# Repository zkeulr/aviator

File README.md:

# README

## Design Document

## To-do

Update design document to reflect final project
Remove DS3231 from parts list in processing subsystem
Update specifications in processing subsystem

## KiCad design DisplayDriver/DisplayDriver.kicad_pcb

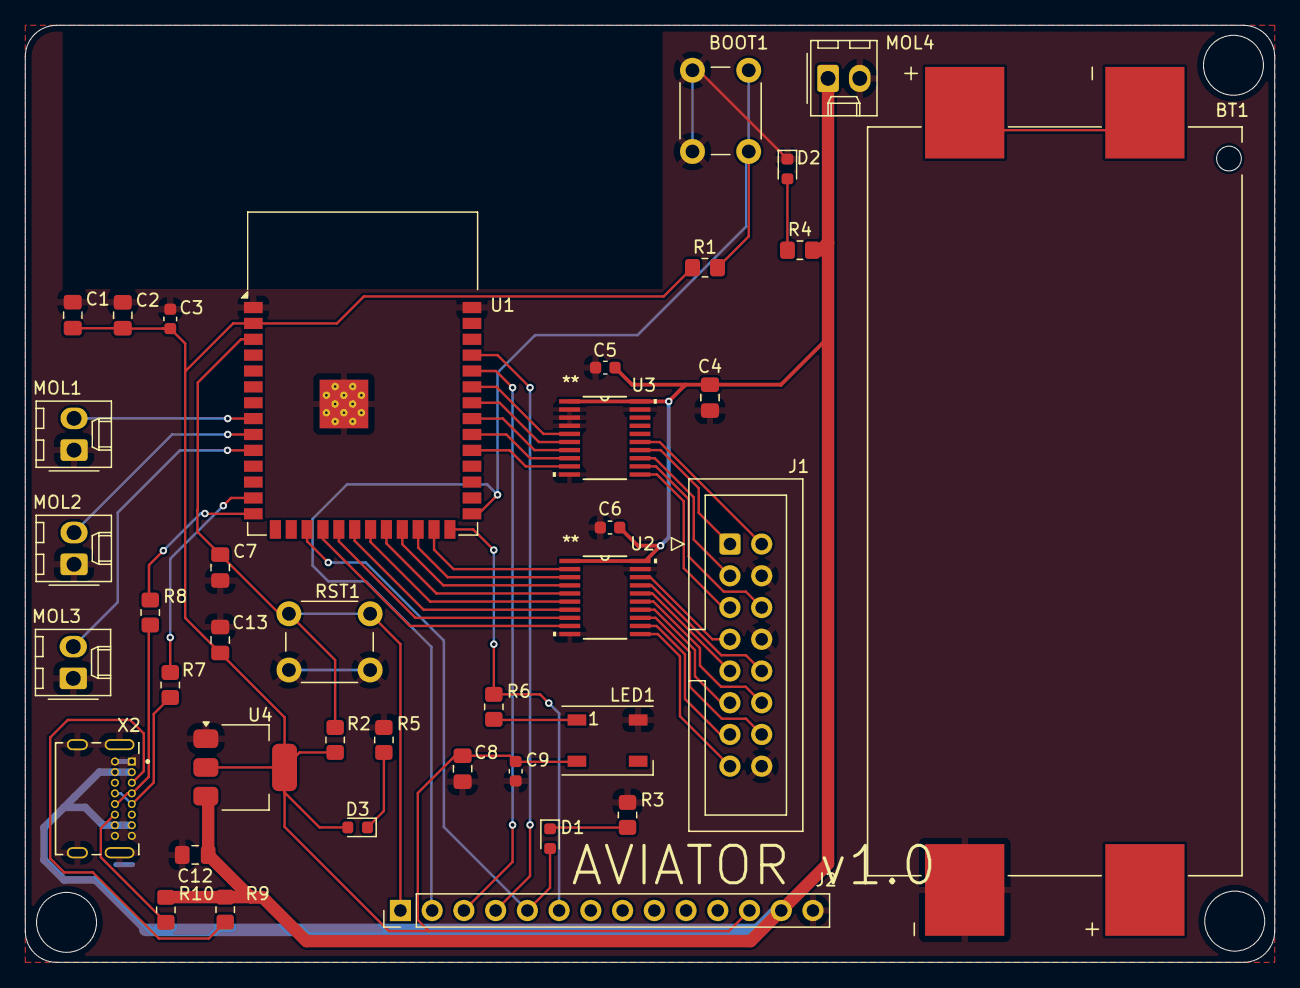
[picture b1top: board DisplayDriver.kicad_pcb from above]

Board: 2 copper layers, 100.0 x 75.0 mm, 39 parts (0 on the bottom side), 49 nets.

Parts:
BOOT1: Lab Kit; SW_PUSH_6mm
BT1: 1012; BAT_1012
C1, C4: 10uF; C_0805_2012Metric_Pad1.18x1.45mm_HandSolder
C2, C7: 1uF; C_0805_2012Metric_Pad1.18x1.45mm_HandSolder
C3, C5, C6, C9: 0.1uF; C_0603_1608Metric
C8: 100uF; C_0805_2012Metric_Pad1.18x1.45mm_HandSolder
C12, C13: C; C_0805_2012Metric_Pad1.18x1.45mm_HandSolder
D1: RED; LED_0603_1608Metric
D2, D3: GREEN; LED_0603_1608Metric
J1: HTSS-108-01-G-D; IDC-Header_2x08_P2.54mm_Vertical
J2: HEADER-1X14; PinHeader_1x14_P2.54mm_Vertical
LED1: LED_WS2812B_PLCC4_5.0x5.0mm_P3.2mm
MOL1, MOL2, MOL3: CASE_SW; Molex_KK-254_AE-6410-02A_1x02_P2.54mm_Vertical
MOL4: Vin; Molex_KK-254_AE-6410-02A_1x02_P2.54mm_Vertical
R1, R2, R3, R4, R5: 10K; R_0805_2012Metric_Pad1.20x1.40mm_HandSolder
R6: 330; R_0805_2012Metric_Pad1.20x1.40mm_HandSolder
R7, R8: 22; R_0805_2012Metric_Pad1.20x1.40mm_HandSolder
R9, R10: 56k; R_0805_2012Metric_Pad1.20x1.40mm_HandSolder
RST1: Lab Kit; SW_PUSH_6mm
U1: ESP32-S3-WROOM-1
U2, U3: 74AHCT245; PW20
U4: AMS1117-3.3; SOT-223-3_TabPin2
X2: UJ20-C-H-G-SMT-TR; CUI_UJ20-C-H-G-SMT-TR

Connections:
3.3V: C1.2, C2.2, C3.1, C8.2, C9.1, C13.1, D3.2 (A), J2.12, LED1.2 (VDD), R1.2, R2.2, U1.2 (3V3), U4.2 (VO)
+5V: C4.2, C5.1, C6.1, C12.1, J2.13, MOL4.1, R4.1, R9.1, R10.2, U2.1 (T/R), U2.20 (VCC), U3.1 (T/R), U3.20 (VCC), U4.3 (VI), X2.A4 (VBUS), X2.A9 (VBUS), X2.B4 (VBUS), X2.B9 (VBUS)
/A0: MOL1.2, U1.8 (IO15)
/A1: MOL2.2, U1.9 (IO16)
/A2: MOL3.2, U1.10 (IO17)
/ADDRA_3V: U1.23 (IO21), U2.4 (A3)
/ADDRB_3V: U1.24 (IO47), U2.3 (A2)
/ADDRC_3V: U1.21 (IO13), U2.6 (A5)
/ADDRD_3V: U1.22 (IO14), U2.5 (A4)
/B1_3V: U1.33 (IO40), U3.7 (A6)
/B2_3V: U1.25 (IO48), U2.2 (A1)
/BOOT0: BOOT1.1, J2.2, R1.1, U1.27 (IO0)
/CC1B: R9.2, X2.A5 (CC1)
/CC2B: R10.1, X2.B5 (CC2)
/CLK: J1.13, U2.12 (B7)
/CLK_3V: U1.19 (IO11), U2.8 (A7)
/D9: D1.2 (A), J2.5, U1.17 (IO9)
/DB+: R8.2, U1.14 (IO20)
/DB-: R7.2, U1.13 (IO19)
/DN_B: R7.1, X2.A7 (DN1), X2.B7 (DN2)
/DP_B: R8.1, X2.A6 (DP1), X2.B6 (DP2)
/G1_3V: U1.35 (IO42), U3.5 (A4)
/G2_3V: U1.32 (IO39), U3.8 (A7)
/LAT: J1.14, U2.13 (B6)
/LAT_3V: U1.20 (IO12), U2.7 (A6)
/M1_A: J1.09, U2.16 (B3)
/M1_B: J1.10, U2.17 (B2)
/M1_B1: J1.03, U3.13 (B6)
/M1_B2: J1.07, U2.18 (B1)
/M1_C: J1.11, U2.14 (B5)
/M1_D: J1.12, U2.15 (B4)
/M1_G1: J1.02, U3.15 (B4)
/M1_G2: J1.06, U3.12 (B7)
/M1_R1: J1.01, U3.14 (B5)
/M1_R2: J1.05, U3.11 (B8)
/NEOPIX: J2.6, R6.1, U1.26 (IO45)
/OE: J1.15, U2.11 (B8)
/OE_3V: U1.18 (IO10), U2.9 (A8)
/R1_3V: U1.34 (IO41), U3.6 (A5)
/R2_3V: U1.31 (IO38), U3.9 (A8)
/UART_RX: J2.3, U1.36 (RXD0)
/UART_TX: J2.4, U1.37 (TXD0)
/~RESET: C7.1, J2.1, R2.1, RST1.2, U1.3 (EN)
GND: BOOT1.2, BT1.N2, C1.1, C2.1, C3.2, C4.1, C5.2, C6.2, C7.2, C8.1, C9.2, C12.2, C13.2, D2.1 (K), J1.04, J1.08, J1.16, J2.14, LED1.4 (GND), MOL1.1, MOL2.1, MOL3.1, MOL4.2, R3.2, R5.2, RST1.1, U1.1 (GND), U1.40 (GND), U1.41 (GND), U2.10 (GND), U2.19 (/OE), U3.2 (A1), U3.3 (A2), U3.4 (A3), U3.10 (GND), U3.19 (/OE), U4.1 (GND), X2.A1 (GND), X2.A12 (GND), X2.B1 (GND), X2.B12 (GND), X2.SH1 (SHIELD), X2.SH2 (SHIELD), X2.SH3 (SHIELD), X2.SH4 (SHIELD)
unnamed: BT1.N1, BT1.P2
unnamed: D1.1 (K), R3.1
unnamed: D2.2 (A), R4.2
unnamed: D3.1 (K), R5.1
unnamed: LED1.1 (DI), R6.2

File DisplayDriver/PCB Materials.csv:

Reference,Value,Footprint,Qty,DNP,Datasheet
5Vin1,Barrel_Jack,,1,,~
"BOOT1,RST1",Lab Kit,Button_Switch_THT:SW_PUSH_6mm,2,,~
BT1,1012,DisplayLibrary:BAT_1012,1,,~
"C1,C4",10uF,Capacitor_SMD:C_0805_2012Metric_Pad1.18x1.45mm_HandSolder,2,,
"C2,C7",1uF,Capacitor_SMD:C_0805_2012Metric_Pad1.18x1.45mm_HandSolder,2,,~
"C3,C5,C6,C9",0.1uF,Capacitor_SMD:C_0603_1608Metric,4,,~
"C8,C10,C11",100uF,Capacitor_SMD:C_0805_2012Metric_Pad1.18x1.45mm_HandSolder,3,,~
"C12,C12B1,C13,C13B1",C,Capacitor_SMD:C_0603_1608Metric,4,,~
D1,RED,LED_SMD:LED_0603_1608Metric,1,,~
"D2,D3",GREEN,LED_SMD:LED_0603_1608Metric,2,,~
J1,HTSS-108-01-G-D,DisplayDriver:IDC-Header_2x08_P2.54mm_Vertical,1,,~
J2,HEADER-1X14,Connector_PinHeader_2.54mm:PinHeader_1x14_P2.54mm_Vertical,1,,~
LED1,~,LED_SMD:LED_WS2812B_PLCC4_5.0x5.0mm_P3.2mm,1,,~
"MOL1,MOL2,MOL3",CASE_SW,Connector_Molex:Molex_KK-254_AE-6410-02A_1x02_P2.54mm_Vertical,3,,~
MOL4,Vin,Connector_Molex:Molex_KK-254_AE-6410-02A_1x02_P2.54mm_Vertical,1,,~
PC1,1000uF/6.3V,Capacitor_SMD:C_0805_2012Metric_Pad1.18x1.45mm_HandSolder,1,,~
"R1,R2,R3,R4,R5",10K,Resistor_SMD:R_0805_2012Metric_Pad1.20x1.40mm_HandSolder,5,,~
R6,330,Resistor_SMD:R_0805_2012Metric_Pad1.20x1.40mm_HandSolder,1,,~
"R7,R8",22,Resistor_SMD:R_0805_2012Metric_Pad1.20x1.40mm_HandSolder,2,,~
"R9,R10",56k,Resistor_SMD:R_0805_2012Metric_Pad1.20x1.40mm_HandSolder,2,,~
U1,ESP32-S3-WROOM-1,RF_Module:ESP32-S3-WROOM-1,1,,https://www.espressif.com/sites/default/files/documentation/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
"U2,U3",74AHCT245,DisplayDriver:PW20,2,,https://www.ti.com/lit/ds/symlink/sn74lvch245a.pdf?HQS=dis-d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
U4,AMS1117-3.3,Package_TO_SOT_SMD:SOT-223-3_TabPin2,1,,http://www.advanced-monolithic.com/pdf/ds1117.pdf
U5,AP2112K-3.3,Package_TO_SOT_SMD:SOT-23-5,1,,https://www.diodes.com/assets/Datasheets/AP2112.pdf
X2,UJ20-C-H-G-SMT-TR,DisplayDriver:CUI_UJ20-C-H-G-SMT-TR,1,,https://www.snapeda.com/parts/UJ20-C-H-G-SMT-TR/Same%20Sky/d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

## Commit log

2025-09-18 Structure
2025-09-18 user stories
2025-09-18 Processing subsystem
2025-09-18 Remove 3d spatial audio from gloassary
2025-09-21 latex format test
2025-09-21 format 2
2025-09-21 format 3
2025-09-21 format 4
2025-09-21 formatted User Stories
2025-09-21 Team Struct. - David
2025-09-21 blockDiagram addition
2025-09-21 half of subsys - David
2025-09-22 final disp subsys push
2025-09-22 Updated with pictures, integrated sections
2025-09-22 Typos
2025-09-22 Rename to aviator
2025-09-23 Added pcb
2025-09-23 Added Design Document 1 PDF
2025-09-30 Linked MicroPython
2025-09-30 Tue Sep 30 12:09:03 EDT 2025
2025-09-30 Tue Sep 30 12:21:21 EDT 2025
2025-09-30 Tue Sep 30 12:22:44 EDT 2025
2025-09-30 Tue Sep 30 13:48:22 EDT 2025
2025-10-02 Stuff
2025-10-02 Disp Driver KiCad Add
2025-10-04 Halfway Disp. Driver for PC work
2025-10-05 Display Driver Schematic - First Prototype
2025-10-05 trim
2025-10-06 Design Doc 2 Final
2025-10-06 clean up for submission
2025-10-06 final
2025-10-07 PCB commit pls
2025-10-09 PC work
2025-10-09 desktop to laptop
2025-10-09 dd from backup
2025-10-09 eod lab thurs
2025-10-10 halfway commit PCB
2025-10-11 PCB wiring
2025-10-11 pt.2
2025-10-13 packaging review submission +gerbers
2025-10-13 Add GNU GPL v3 license
    Added the GNU General Public License version 3 to the project.
2025-10-15 PD Chip addition, proper schematic for Breadboarding today
2025-10-15 disp. driver .py
2025-10-15 dev-pinmap
2025-10-16 Thu Oct 16 10:37:04 EDT 2025
2025-10-16 dfslahfd
2025-10-16 Message
2025-10-16 asdfsd
2025-10-23 Removed micropython
2025-10-23 Reverted code.py
2025-10-24 Major PCB Revisions.
2025-10-27 random
2025-10-28 jsvdbjkvb
2025-10-28 aaa
    aaa
2025-10-28 aaa
    aa
2025-10-29 bat footprint
2025-10-30 settings.toml
2025-10-30 PCB skjdcnsjk
2025-10-30 lap to PC
2025-10-30 change the ****** shifter footprint
2025-11-04 PC to lap
2025-11-05 I swear this is the last PCB revision
2025-11-05 bill of mat.
2025-11-05 pcb review prep
2025-11-05 pre-procurement
2025-11-06 JLCPCB audit correction
2025-11-06 audit additions (drill files)
2025-11-11 minor DD alterations
2025-11-13 display_pixels
2025-11-19 Started DD3
2025-11-20 ascdisudna
2025-11-20 sadcdscs
2025-11-20 docs to pc
2025-11-20 DD3 final DT
2025-12-06 Mian
2025-12-07 DD3 (+josh stuff)
2025-12-07 Removed strong typing from adsb.py due to lack of support on CircuitPython, minor changes to code.py to change color of weather text based on temp
2025-12-07 aa
    aa
2025-12-08 Tweaks
2025-12-09 Emoji
2025-12-13 Sketch
2025-12-13 Removed labels for design document iterations
2025-12-13 Added table of figures and contents
2025-12-14 Add files via upload
    This is the final design document I am submitting on BS (Josh)
